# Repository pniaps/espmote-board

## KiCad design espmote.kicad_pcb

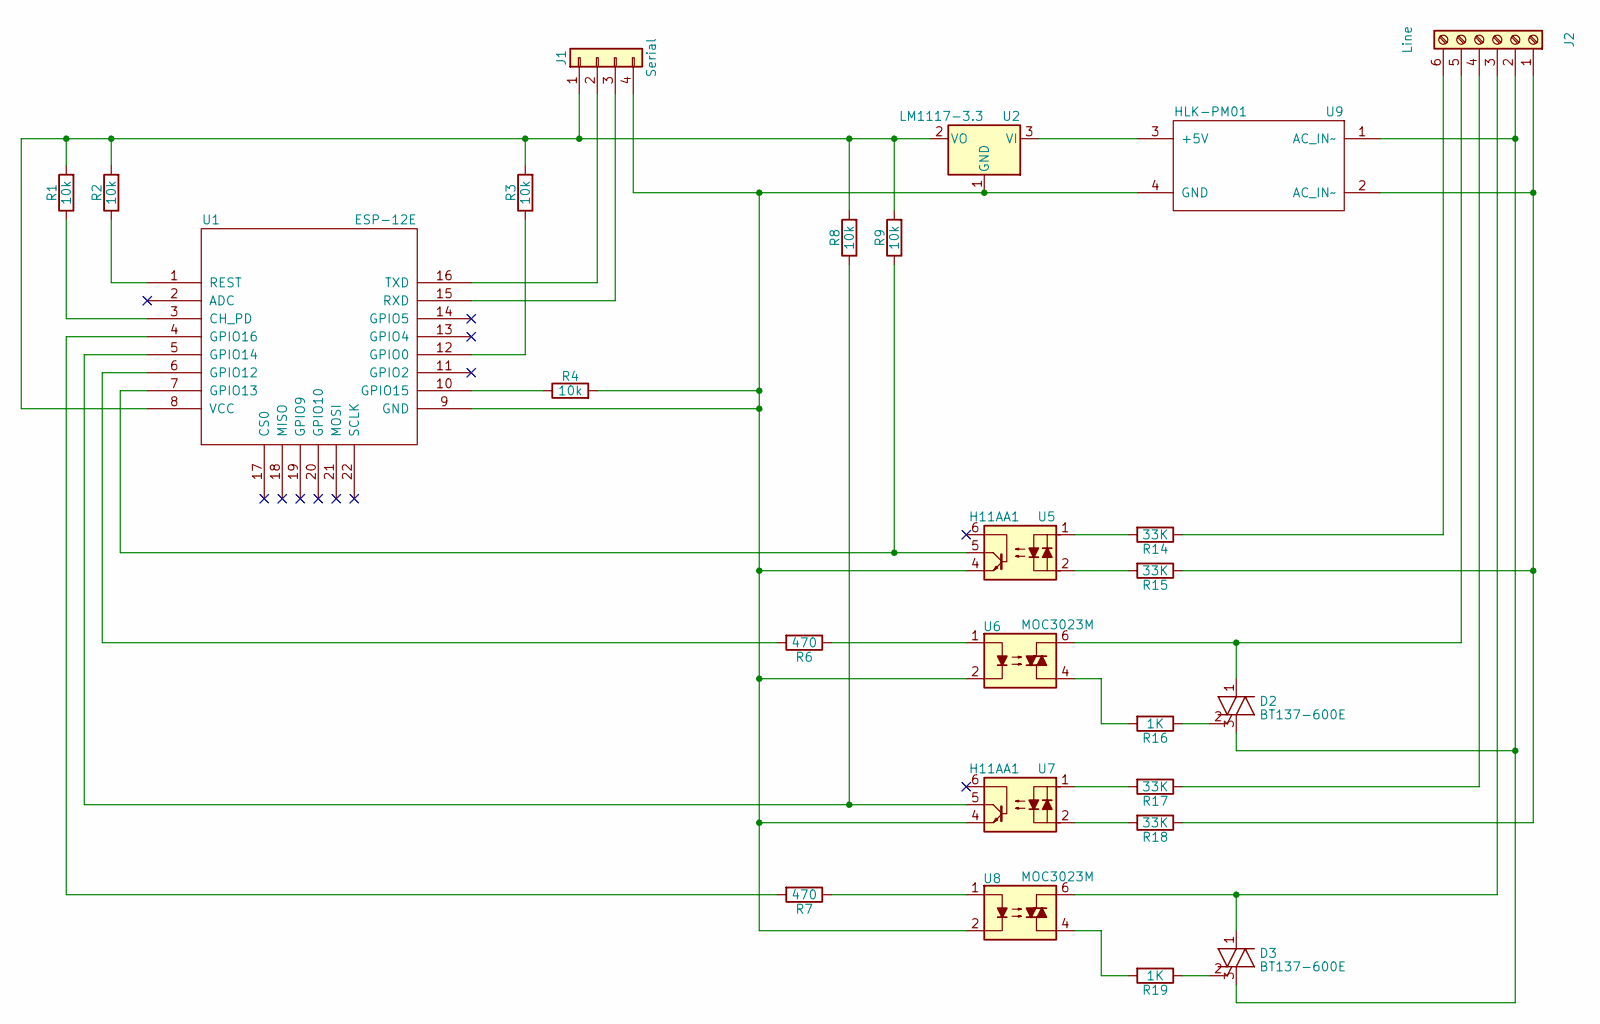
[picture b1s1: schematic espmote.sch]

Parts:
D2, D3: BT137-600E; TO-220_Vertical
J1: Serial; Pin_Header_Straight_1x04_Pitch2.54mm
J2: Line; TerminalBlock_Pheonix_MKDS1.5-6pol
R1, R2, R3, R4, R8, R9: 10k; R_1206_HandSoldering
R6, R7: 470; R_1206_HandSoldering
R14, R15, R17, R18: 33K; R_2512_HandSoldering
R16, R19: 1K; R_1206_HandSoldering
U1: ESP-12E
U2: LM1117-3.3; TO-220_Vertical
U5, U7: H11AA1; DIP-6_W7.62mm
U6, U8: MOC3023M; DIP-6_W7.62mm
U9: HLK-PM01

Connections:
unnamed: D2.1 (A1), J2.5, U6.6
unnamed: D2.2 (G), R16.1
unnamed: D2.3 (A2), D3.3 (A2), J2.2, U9.1 (AC_IN~~)
unnamed: D3.1 (A1), J2.3, U8.6
unnamed: D3.2 (G), R19.1
unnamed: J1.1, R1.2, R2.2, R3.2, R8.2, R9.2, U1.8 (VCC), U2.2 (VO)
unnamed: J1.2, U1.16 (TXD)
unnamed: J1.3, U1.15 (RXD)
unnamed: J1.4, R4.2, U1.9 (GND), U2.1 (GND), U5.4, U6.2, U7.4, U8.2, U9.4 (GND)
unnamed: J2.1, R15.1, R18.1, U9.2 (AC_IN~~)
unnamed: J2.4, R17.1
unnamed: J2.6, R14.1
unnamed: R1.1, U1.3 (CH_PD)
unnamed: R2.1, U1.1 (REST)
unnamed: R3.1, U1.12 (GPIO0)
unnamed: R4.1, U1.10 (GPIO15)
unnamed: R6.1, U6.1
unnamed: R6.2, U1.6 (GPIO12)
unnamed: R7.1, U8.1
unnamed: R7.2, U1.4 (GPIO16)
unnamed: R8.1, U1.5 (GPIO14), U7.5
unnamed: R9.1, U1.7 (GPIO13), U5.5
unnamed: R14.2, U5.1
unnamed: R15.2, U5.2
unnamed: R16.2, U6.4
unnamed: R17.2, U7.1
unnamed: R18.2, U7.2
unnamed: R19.2, U8.4
unnamed: U2.3 (VI), U9.3 (+5V)

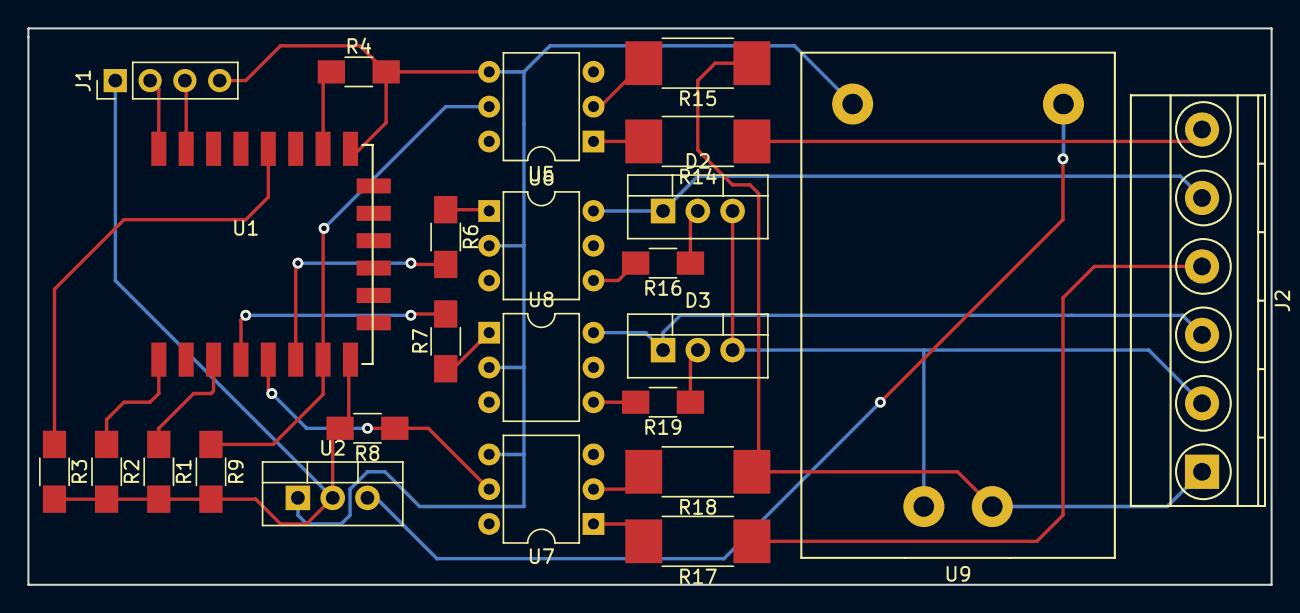
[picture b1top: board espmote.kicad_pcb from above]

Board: 2 copper layers, 90.8 x 40.6 mm, 25 parts (0 on the bottom side), 29 nets.

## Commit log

2017-08-08 Added Connection draw.io
2017-08-08 Added connection_before.jpg
2017-08-08 Added connection_after.jpg
2017-08-31 Add schema
2017-08-31 Change pniaps_lib to pnips_kicad
2017-09-05 Use ESP-12E component from pniaps library
2017-09-05 Rename pniaps_kicad library to pniaps
2017-09-14 two channels and pcb
2017-11-08 Remove detectors
